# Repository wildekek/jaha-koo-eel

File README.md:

# Jaha Koo Eel

A robotic remote controlled eel. A prop for the play [Haribo Kimchi](https://www.campo.nu/en/production/24342/haribo_kimchi).

A collaboration between [Adriaan Wormgoor](http://adriaanwormgoor.nl) and [Willem Vooijs](https://willem.vooijs.eu), produced for [Stichting Theater Utrecht](https://www.theaterutrecht.nl/innovationlab) and [Campo](https://campo.nu).

## Build your own
[Bill of Materials](./BOM.md)

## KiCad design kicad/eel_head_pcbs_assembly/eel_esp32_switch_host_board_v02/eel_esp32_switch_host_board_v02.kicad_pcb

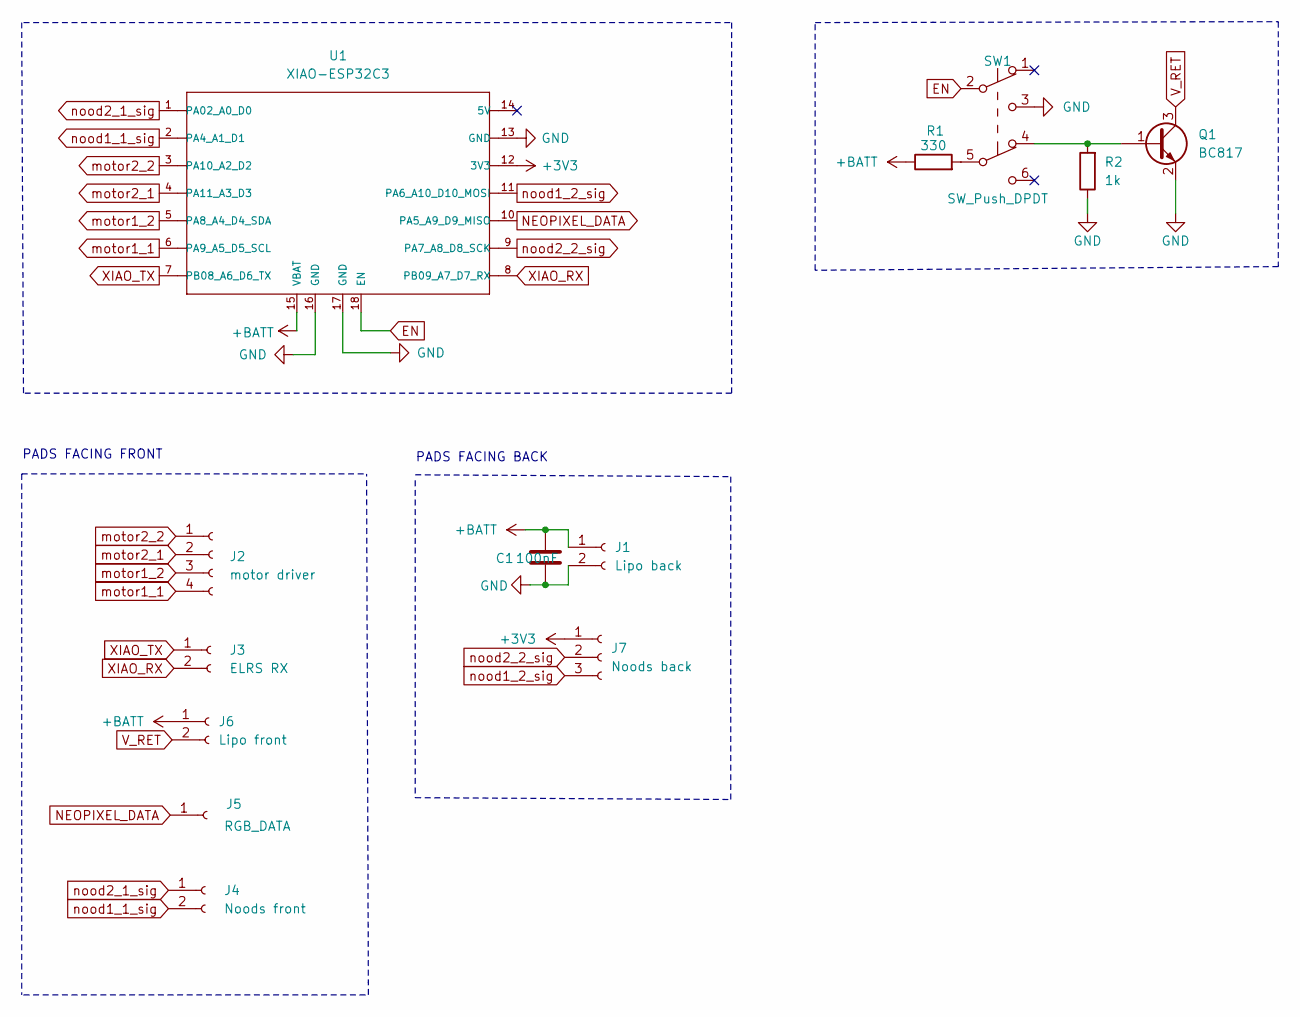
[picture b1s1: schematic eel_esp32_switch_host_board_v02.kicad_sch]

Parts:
C1: 100nF; C_0805_2012Metric_Pad1.18x1.45mm_HandSolder
J1: Lipo back; smd_solder_pads_1x02_2.54mm
J2: motor driver; smd_solder_pads_1x04
J3: ELRS RX; smd_solder_pads_1x02_2.54mm
J4: Noods front; smd_solder_pads_1x02_2.54mm
J5: RGB_DATA; smd_solder_pads_1x01_2.54mm
J6: Lipo front; smd_solder_pads_1x02_2.54mm
J7: Noods back; smd_solder_pads_1x03_n00ds_v1
Q1: BC817; SOT-23
R1: 330; R_0805_2012Metric_Pad1.20x1.40mm_HandSolder
R2: 1k; R_0805_2012Metric_Pad1.20x1.40mm_HandSolder
SW1: SW_Push_DPDT; Nidec_2x03_dpdt_CL-SB-22B-11
U1: XIAO-ESP32C3; MOUDLE14P-SMD-2.54-21X17.8MM

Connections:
+3V3: J7.1, U1.12 (3V3)
+BATT: C1.1, J1.1, J6.1, R1.1, U1.15 (VBAT)
EN: SW1.2 (B), U1.18 (EN)
GND: C1.2, J1.2, Q1.2 (E), R2.1, SW1.3 (C), U1.13 (GND), U1.16 (GND), U1.17 (GND)
NEOPIXEL_DATA: J5.1, U1.10 (PA5_A9_D9_MISO)
unnamed: Q1.1 (B), R2.2, SW1.4 (A)
unnamed: R1.2, SW1.5 (B)
V_RET: J6.2, Q1.3 (C)
XIAO_RX: J3.2, U1.8 (PB09_A7_D7_RX)
XIAO_TX: J3.1, U1.7 (PB08_A6_D6_TX)
motor1_1: J2.4, U1.6 (PA9_A5_D5_SCL)
motor1_2: J2.3, U1.5 (PA8_A4_D4_SDA)
motor2_1: J2.2, U1.4 (PA11_A3_D3)
motor2_2: J2.1, U1.3 (PA10_A2_D2)
nood1_1_sig: J4.2, U1.2 (PA4_A1_D1)
nood1_2_sig: J7.3, U1.11 (PA6_A10_D10_MOSI)
nood2_1_sig: J4.1, U1.1 (PA02_A0_D0)
nood2_2_sig: J7.2, U1.9 (PA7_A8_D8_SCK)

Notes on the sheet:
PADS FACING BACK
PADS FACING FRONT

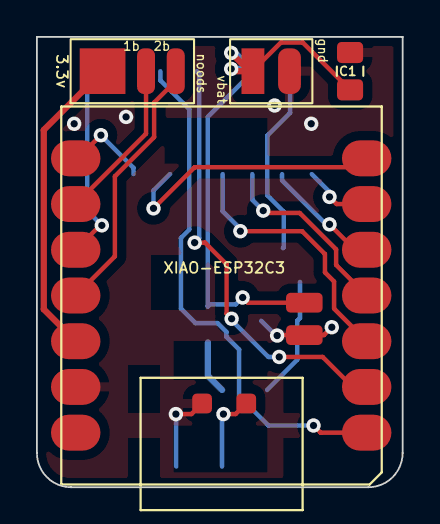
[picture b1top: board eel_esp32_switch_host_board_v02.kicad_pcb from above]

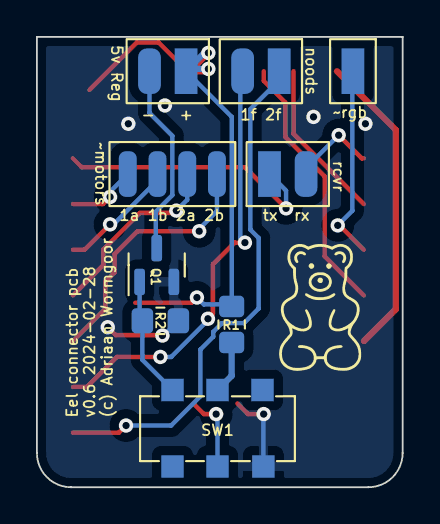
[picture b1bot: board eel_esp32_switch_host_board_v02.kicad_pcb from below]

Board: 2 copper layers, 20.3 x 25.0 mm, 13 parts (9 on the bottom side), 18 nets.

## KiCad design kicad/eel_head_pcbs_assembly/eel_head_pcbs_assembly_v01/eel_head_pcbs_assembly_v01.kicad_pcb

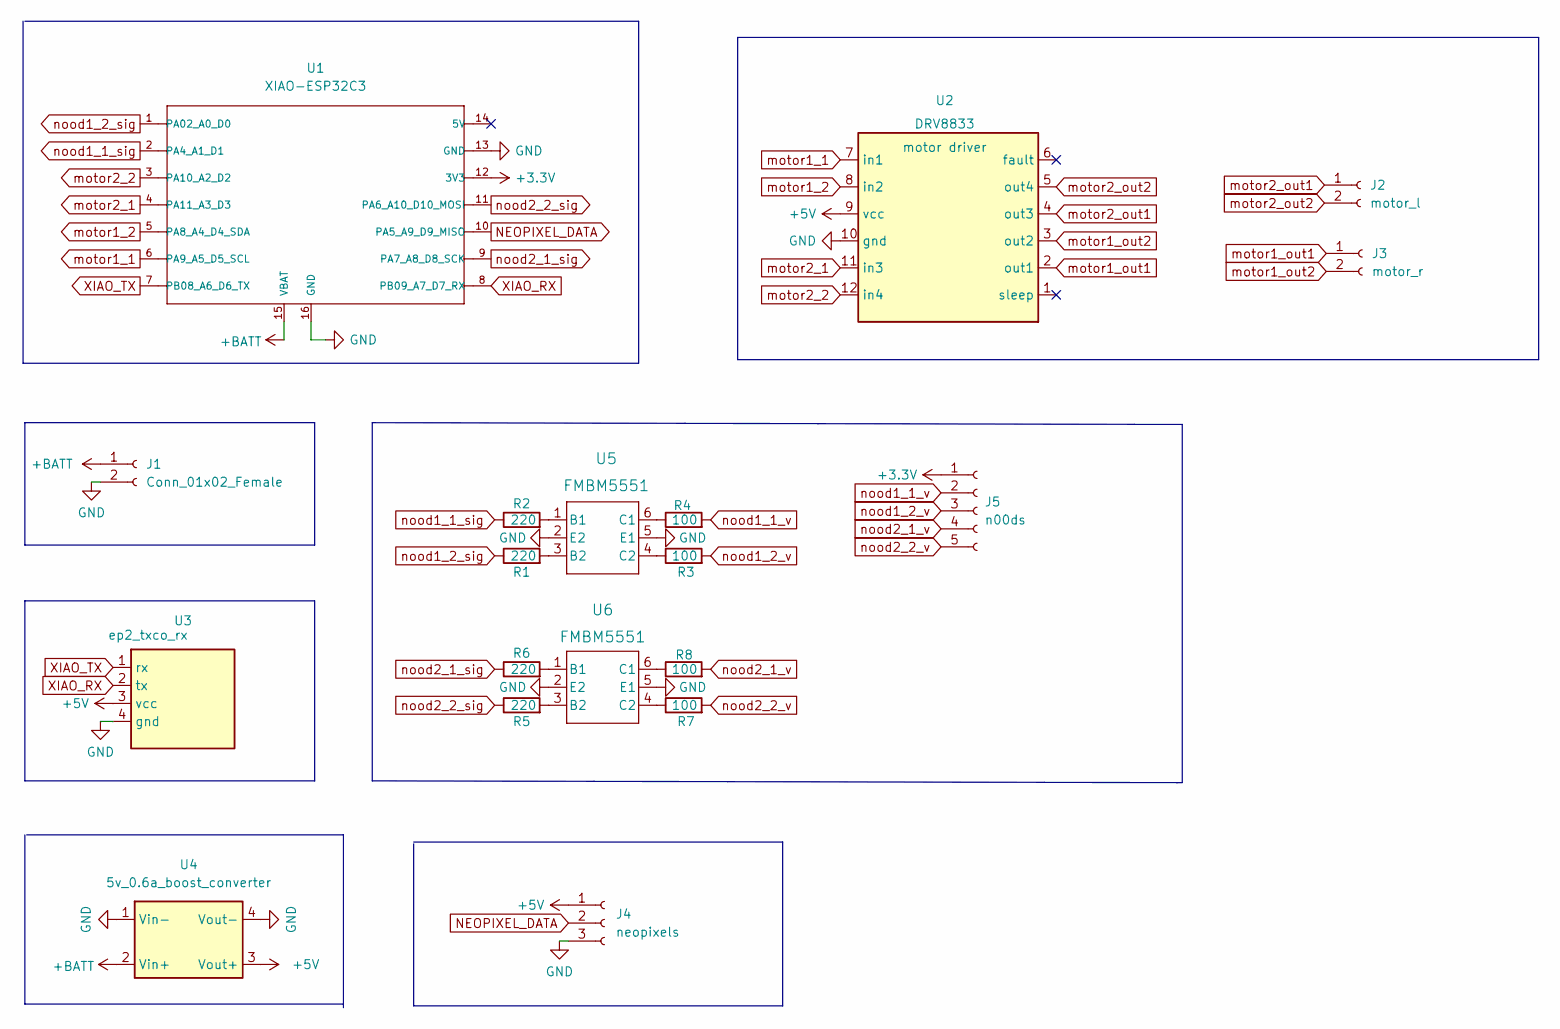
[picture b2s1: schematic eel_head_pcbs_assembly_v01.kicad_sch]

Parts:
J1: Conn_01x02_Female; JST_PH_S2B-PH-K_1x02_P2.00mm_Horizontal
J2: motor_l; smd_solder_pads_1x02_2.54mm
J3: motor_r; smd_solder_pads_1x02_2.54mm
J4: neopixels; smd_solder_pads_1x03_2.54mm
J5: n00ds; smd_solder_pads_1x05_n00ds_2.54mm
R1, R2, R5, R6: 220; R_0603_1608Metric_Pad0.98x0.95mm_HandSolder
R3, R4, R7, R8: 100; R_0603_1608Metric_Pad0.98x0.95mm_HandSolder
U1: XIAO-ESP32C3; MOUDLE14P-SMD-2.54-21X17.8MM
U2: DRV8833; drv8833_breakout
U3: ep2_txco_rx; happymodel_ep2_txco_rx
U4: 5v_0.6a_boost_converter
U5, U6: FMBM5551; SSOT6_3X1P7_ONS

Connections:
+3V3: J5.1, U1.12 (3V3)
+5V: J4.1, U2.9 (vcc), U3.3 (vcc), U4.3 (Vout+)
+BATT: J1.1, U1.15 (VBAT), U4.2 (Vin+)
GND: J1.2, J4.3, U1.13 (GND), U1.16 (GND), U2.10 (gnd), U3.4 (gnd), U4.1 (Vin-), U4.4 (Vout-), U5.2 (E2), U5.5 (E1), U6.2 (E2), U6.5 (E1)
NEOPIXEL_DATA: J4.2, U1.10 (PA5_A9_D9_MISO)
unnamed: R1.2, U5.3 (B2)
unnamed: R2.2, U5.1 (B1)
unnamed: R3.1, U5.4 (C2)
unnamed: R4.1, U5.6 (C1)
unnamed: R5.2, U6.3 (B2)
unnamed: R6.2, U6.1 (B1)
unnamed: R7.1, U6.4 (C2)
unnamed: R8.1, U6.6 (C1)
XIAO_RX: U1.8 (PB09_A7_D7_RX), U3.2 (tx)
XIAO_TX: U1.7 (PB08_A6_D6_TX), U3.1 (rx)
motor1_1: U1.6 (PA9_A5_D5_SCL), U2.7 (in1)
motor1_2: U1.5 (PA8_A4_D4_SDA), U2.8 (in2)
motor1_out1: J3.1, U2.2 (out1)
motor1_out2: J3.2, U2.3 (out2)
motor2_1: U1.4 (PA11_A3_D3), U2.11 (in3)
motor2_2: U1.3 (PA10_A2_D2), U2.12 (in4)
motor2_out1: J2.1, U2.4 (out3)
motor2_out2: J2.2, U2.5 (out4)
nood1_1_sig: R2.1, U1.2 (PA4_A1_D1)
nood1_1_v: J5.2, R4.2
nood1_2_sig: R1.1, U1.1 (PA02_A0_D0)
nood1_2_v: J5.3, R3.2
nood2_1_sig: R6.1, U1.9 (PA7_A8_D8_SCK)
nood2_1_v: J5.4, R8.2
nood2_2_sig: R5.1, U1.11 (PA6_A10_D10_MOSI)
nood2_2_v: J5.5, R7.2

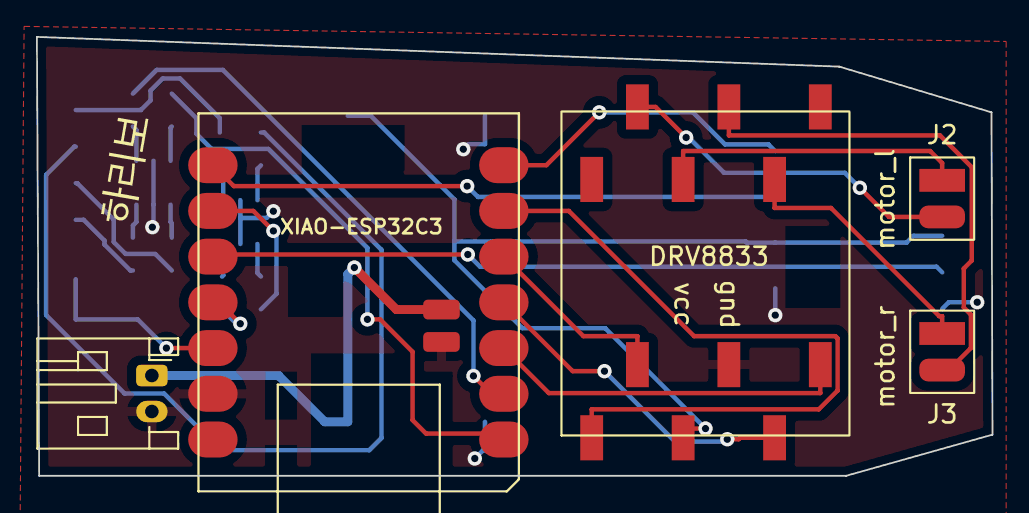
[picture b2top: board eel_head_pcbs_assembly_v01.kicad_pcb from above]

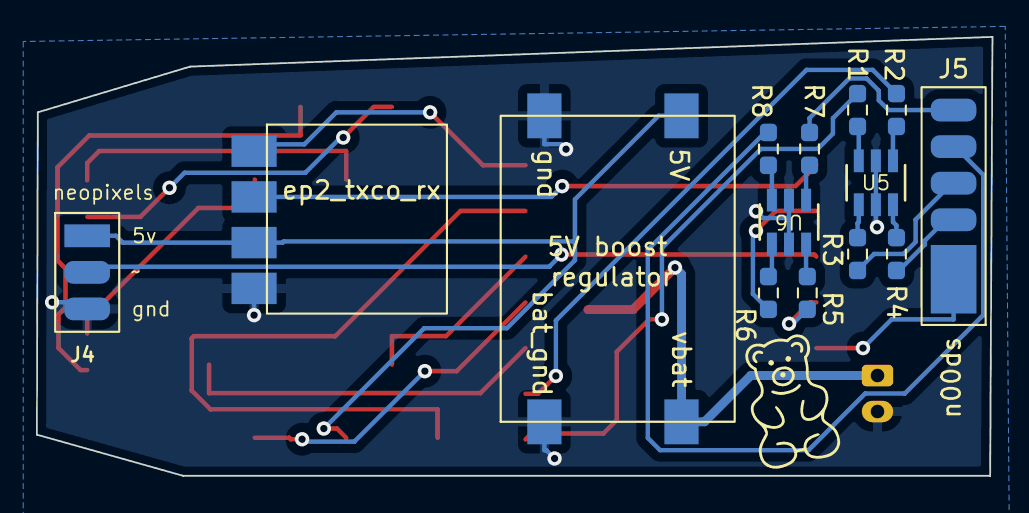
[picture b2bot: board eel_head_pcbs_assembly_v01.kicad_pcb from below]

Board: 2 copper layers, 53.1 x 24.4 mm, 21 parts (15 on the bottom side), 31 nets.

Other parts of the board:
haribo_korean: LOGO; haribo_in_korean_3.2mm
logo_haribo_bear: LOGO; haribo_outline_bw_8mm

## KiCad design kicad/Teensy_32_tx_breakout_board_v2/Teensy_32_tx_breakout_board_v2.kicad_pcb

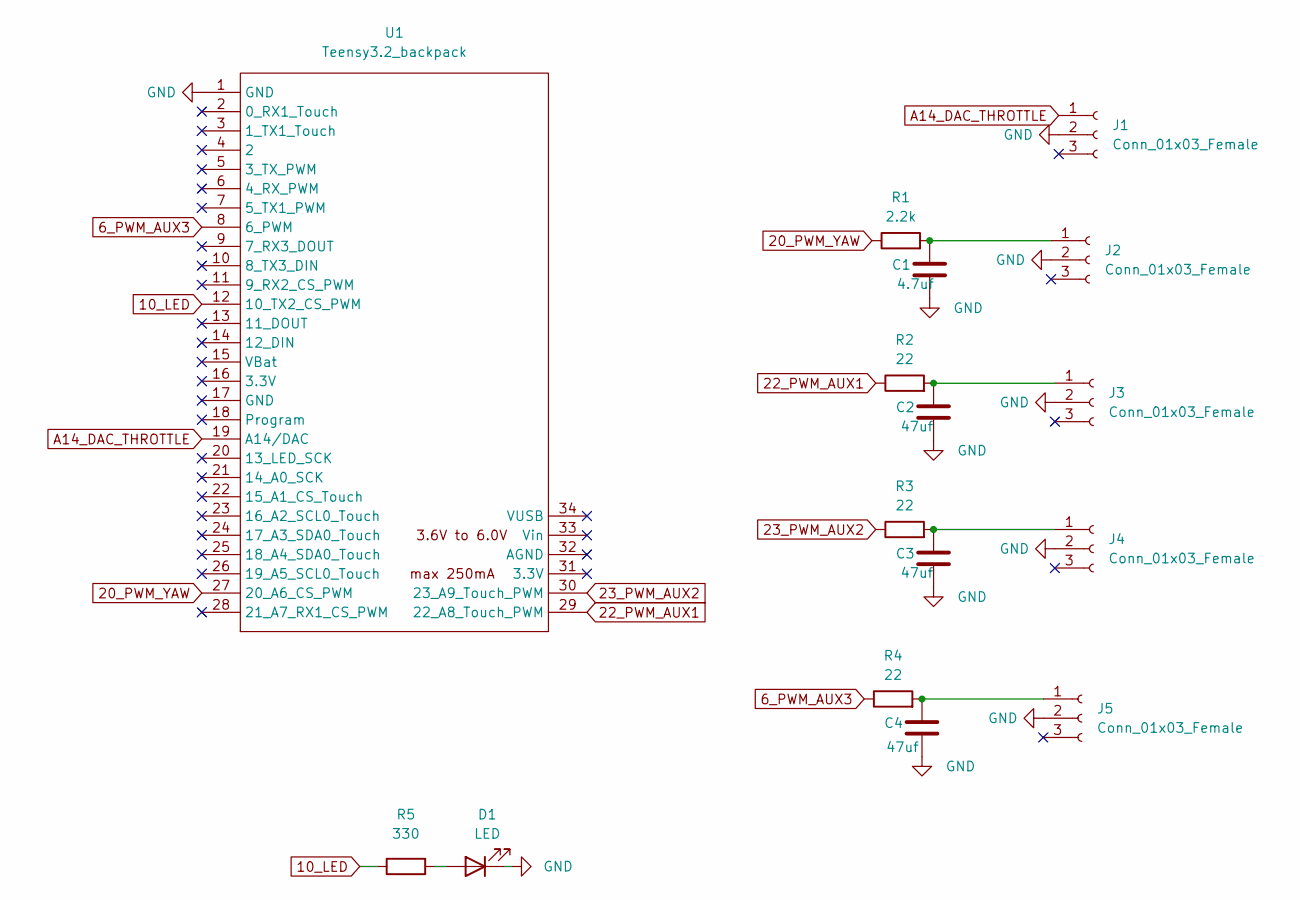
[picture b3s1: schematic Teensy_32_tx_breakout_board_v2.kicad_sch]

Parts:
C1: 4.7uf; C_0603_1608Metric
C2, C3, C4: 47uf; C_0603_1608Metric
D1: LED; LED_1206_3216Metric
J1, J2, J3, J4, J5: Conn_01x03_Female; JST_SH_BM03B-SRSS-TB_1x03-1MP_P1.00mm_Vertical
R1: 2.2k; R_0603_1608Metric
R2, R3, R4: 22; R_0603_1608Metric
R5: 330; R_1206_3216Metric
U1: Teensy3.2_backpack; Teensy30_31_32_outside_pins

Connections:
6_PWM_AUX3: R4.1, U1.8 (6_PWM)
10_LED: R5.1, U1.12 (10_TX2_CS_PWM)
20_PWM_YAW: R1.1, U1.27 (20_A6_CS_PWM)
22_PWM_AUX1: R2.1, U1.29 (22_A8_Touch_PWM)
23_PWM_AUX2: R3.1, U1.30 (23_A9_Touch_PWM)
A14_DAC_THROTTLE: J1.1, U1.19 (A14/DAC)
GND: C1.2, C2.2, C3.2, C4.2, D1.2 (K), J1.2, J2.2, J3.2, J4.2, J5.2, U1.1 (GND)
unnamed: C1.1, J2.1, R1.2
unnamed: C2.1, J3.1, R2.2
unnamed: C3.1, J4.1, R3.2
unnamed: C4.1, J5.1, R4.2
unnamed: D1.1 (A), R5.2

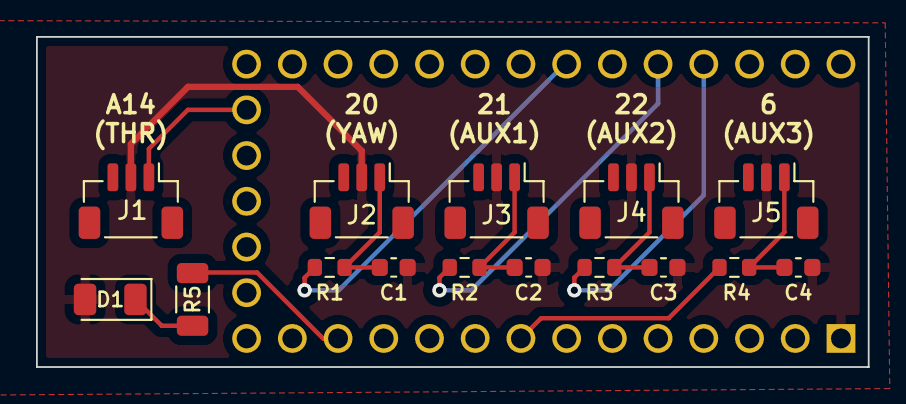
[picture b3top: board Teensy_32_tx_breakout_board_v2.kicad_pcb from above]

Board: 2 copper layers, 46.2 x 18.3 mm, 16 parts (1 on the bottom side), 12 nets.

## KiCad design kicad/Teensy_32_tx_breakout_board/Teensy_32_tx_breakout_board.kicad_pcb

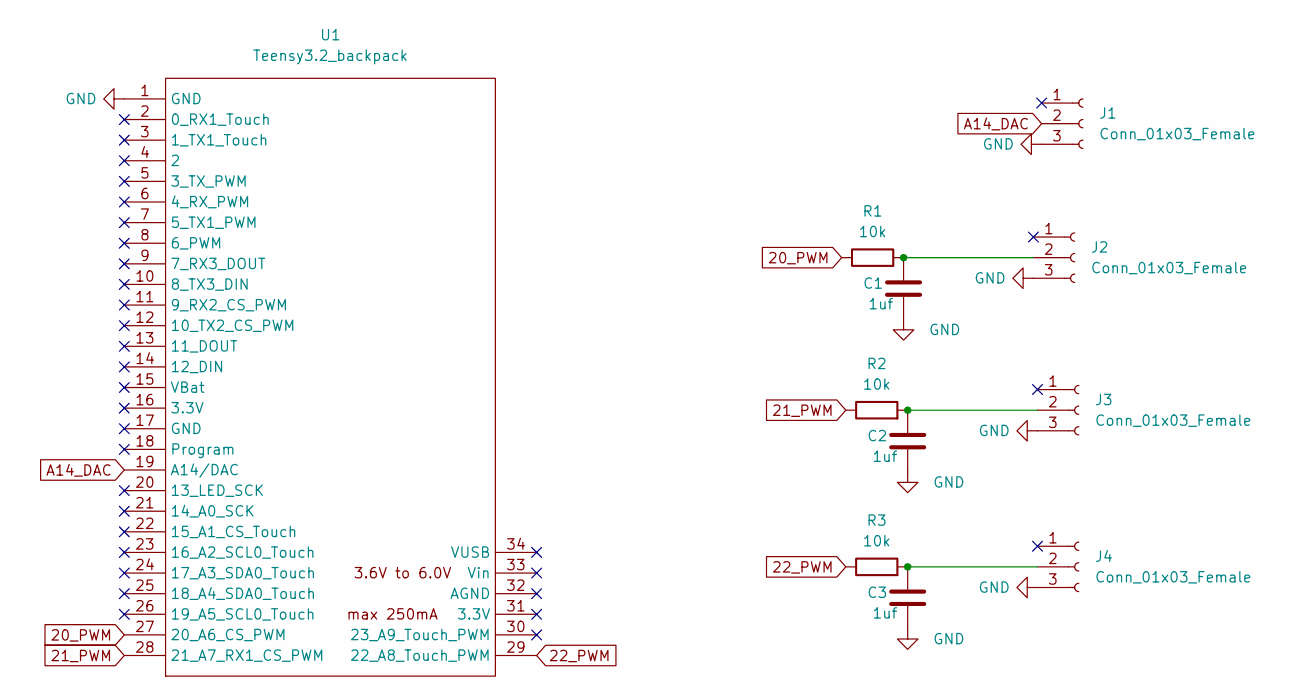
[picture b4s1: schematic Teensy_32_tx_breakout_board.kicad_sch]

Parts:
C1, C2, C3: 1uf; C_0603_1608Metric
J1, J2, J3, J4: Conn_01x03_Female; JST_SH_BM03B-SRSS-TB_1x03-1MP_P1.00mm_Vertical
R1, R2, R3: 10k; R_0603_1608Metric
U1: Teensy3.2_backpack; Teensy30_31_32_outside_pins

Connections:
20_PWM: R1.1, U1.27 (20_A6_CS_PWM)
21_PWM: R2.1, U1.28 (21_A7_RX1_CS_PWM)
22_PWM: R3.1, U1.29 (22_A8_Touch_PWM)
A14_DAC: J1.2, U1.19 (A14/DAC)
GND: C1.2, C2.2, C3.2, J1.3, J2.3, J3.3, J4.3, U1.1 (GND)
unnamed: C1.1, J2.2, R1.2
unnamed: C2.1, J3.2, R2.2
unnamed: C3.1, J4.2, R3.2

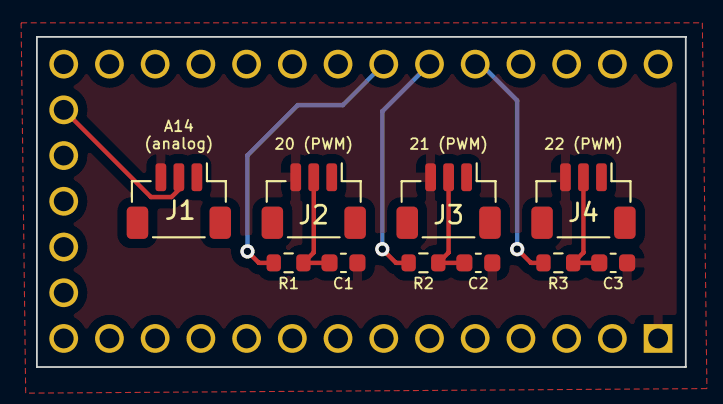
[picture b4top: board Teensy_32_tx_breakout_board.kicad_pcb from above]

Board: 2 copper layers, 36.1 x 18.3 mm, 11 parts (1 on the bottom side), 8 nets.

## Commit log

2023-12-13 first commit of esp32-c3 pio project
2023-12-13 expand to 2 motor control
2023-12-14 implement correct rx control mapping to motors
2023-12-15 add a few test sketches to research a led flickering control issue
2023-12-15 add Teensy project (doesn't work yet)
2024-01-18 add Teensy breakout board PCB
2024-01-18 add xiao esp32c3 project (so far)
2024-01-18 add some Teensy code
2024-02-03 add xiao esp32c3 footprint
2024-02-03 create teensy breakout v2
2024-02-03 add a few pcb gfx
2024-02-03 add footprints for head pcb
2024-02-03 create symbols for head pcb
2024-02-03 create actual v1 of head pcb
2024-02-03 create v2 of head pcb
2024-02-03 create v3 of head pcb
2024-02-03 create teensy test sketch - midi directly to buitlin-led
2024-02-03 create test sketch to review sin-offset effect for n00ds
2024-02-03 update teensy main sketch
2024-02-03 Update Jaha Koo Eel - git.code-workspace
2024-02-20 test: address motors directly with ledcWrite
2024-02-20 mainly: rename environment names
2024-02-20 debug sketch: test motor control with new class
2024-02-20 test sketch: sbus-receive signals and translate to n00ds ledc out
2024-02-20 test sketch: add one motor with direct ledcWrite
2024-02-20 test sketch: address two motors with new external class
2024-02-20 test sketch: locally control n00ds with direct ledcWrite
2024-02-21 add invert direction option
2024-02-22 clean up code
2024-02-23 create custom footprints
2024-02-23 rename sketch
2024-02-23 update crsf lib
2024-02-27 add project for driving ELRS tx (CRSF)
2024-02-27 formatting
2024-02-27 cleanup
2024-02-29 adjust courtyard
2024-02-29 fix motor reverse error
2024-02-29 fix motor direction bug
2024-02-29 move motor vals calc to its own method
2024-02-29 partial implementation of state machine
2024-03-07 update 3d model references for footprints
2024-03-07 update xiao pcb
2024-03-07 create noods test sketch
2024-03-07 update noods test sketch
2024-03-07 fix incorrect 'motor reverse' approach
2024-03-13 cleanup unused code
2024-03-14 final updates before handover
2024-04-03 Separated motor mount
2024-04-03 Add mouth light guide multi material
2024-04-03 Fix readme errors
2024-04-03 Deeper motor mount grooves
2024-04-03 Add Switch cap
2024-04-03 Switch cap to fine
2024-04-10 create midi host sketches
2024-04-10 Increase quality with wall thickness
2024-04-10 Reduce motor mount ridge height
2024-04-17 Update BOM with extra n00d segment
2024-04-17 change pin assignment (minor)
2024-05-03 add VSCode project for esp32s3 as host for elrs tx module
2024-05-03 define which board uses these pins
2024-05-03 set default values for AETR at start of program.
2024-05-03 add simple sbus rx print sketch
2024-05-03 add a lot of toad dynamixel-driving sketches
2024-05-03 add two Dynamixel Arduino libraries
2024-11-13 Add eye light guide
2025-11-13 Add CAD source files
2025-11-18 move interactive BOM
2025-11-19 add organized exported pcb/schematic assets
2025-11-19 organize exported assets of some of the Kicad projects
2025-11-19 update Arduino README
